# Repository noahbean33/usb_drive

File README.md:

# Smart USB Thumb Drive — 64 GB, 4-Layer PCB (KiCad)

A fully routed, manufacture-ready 64 GB USB thumb drive PCB designed from scratch in KiCad. This project demonstrates high-speed digital design, BGA escape routing, impedance-controlled differential pairs, and multi-layer power distribution — all within the physical constraints of a standard USB stick form factor.

## What This Project Is

This is a complete hardware design for a "smart" USB thumb drive built around:

- **RP2040** — Dual-core Arm Cortex-M0+ microcontroller (Raspberry Pi silicon)
- **MTFC64GAPALBH-IT** — 64 GB eMMC NAND flash in a 153-ball TFBGA package (0.5 mm pitch)
- **USB2244** — USB 2.0 to eMMC bridge controller
- **SY8253ADC** — Synchronous buck converter for regulated power
- **LM66100** — Dual ideal-diode OR-ing circuit for power path management
- **INA226** — High-side/low-side current and power monitor (I2C)
- **SSD1306** — 0.91" 128×32 OLED display for status readout
- **TMP119** — Digital temperature sensor
- **TVS diode arrays** — ESD protection on both USB ports

The drive is not just storage — the RP2040 provides programmable logic for monitoring power draw, temperature, and storage status via the OLED, making it a platform for embedded USB experimentation.

## How It Works

### Architecture

The schematic is split into hierarchical sheets for modularity:

| Sheet | Function |
|-------|----------|
| `oring_power` | Dual ideal-diode OR-ing (VBUS vs. external supply) |
| `buck_converter_power` | 3.3 V regulated rail from the OR'd input |
| `usb_bridge` | USB2244 bridge + ESD protection |
| `emmc_storage` | 64 GB eMMC with full 8-bit data bus |
| `rp2040` | MCU core, crystal, SWD, boot circuitry |
| `sensors` | INA226 current monitor + TMP119 temperature sensor |
| `gpio` | RP2040 breakout headers for development |

### PCB Stackup (4 layers)

| Layer | Purpose |
|-------|---------|
| F.Cu | Signal routing (USB diff pairs, eMMC data bus) |
| In1.Cu | Solid ground plane |
| In2.Cu | Power distribution plane |
| B.Cu | Signal routing (secondary) |

The dedicated ground and power planes provide low-impedance return paths and controlled impedance for high-speed signals.

## Key Design Decisions

### 1. BGA Escape Routing (Via-in-Pad)

The 153-ball eMMC package at 0.5 mm pitch cannot be escaped with surface traces alone. I used **via-in-pad** with 0.3 mm diameter / 0.15 mm drill vias placed directly on BGA pads, transitioning signals to inner layers. Custom DRC rules relax annular width minimums (0.075 mm) and clearances specifically within the BGA courtyard to allow this dense routing while maintaining DRC coverage everywhere else.

### 2. Impedance-Controlled USB 2.0 Differential Pairs

USB D+/D− pairs are routed as impedance-controlled differential pairs targeting 90 Ω differential impedance. Trace geometry was calculated using a stack-up impedance tool and verified against the fabricator's capabilities. Tight coupling is maintained throughout the route.

### 3. eMMC Data Bus Length Matching

The 8-bit parallel eMMC data bus is length-matched to ±3 mm (data lines) and ±5 mm (clock), meeting timing requirements for HS400-class operation. KiCad's tuning patterns (meander routing) are applied with 80% corner radius to minimize reflections.

### 4. Dual Ideal-Diode Power OR-ing

Rather than a simple regulator off VBUS, the power architecture uses two TI LM66100 ideal diodes in an OR-ing configuration. This allows the board to be powered from either USB port seamlessly, with near-zero reverse current and minimal voltage drop — critical for a bus-powered device with tight power budgets.

### 5. Custom DRC Rules

Instead of globally weakening design rules to accommodate BGA and fine-pitch ICs, I wrote **per-component DRC exceptions** in KiCad's custom rules language. Each rule is scoped by courtyard (`insideCourtyard`) so that strict defaults (0.1 mm clearance, standard annular widths) apply everywhere except where the design explicitly requires tighter geometry.

### 6. Teardrops and Reliability Features

Teardrops are enabled on all vias, PTH pads, and SMD pads to improve mechanical robustness and reduce stress risers during thermal cycling — important for a device that will be repeatedly plugged and unplugged.

## Repository Structure

```
├── Smart USB Drive - Course.kicad_pro    # KiCad project file
├── Smart USB Drive - Course.kicad_sch    # Top-level schematic
├── Smart USB Drive - Course.kicad_pcb    # PCB layout
├── Smart USB Drive - Course.kicad_dru    # Custom design rules
├── oring_power.kicad_sch                 # Power OR-ing sub-sheet
├── buck_converter_power.kicad_sch        # Buck converter sub-sheet
├── usb_bridge.kicad_sch                  # USB bridge sub-sheet
├── emmc_storage.kicad_sch                # eMMC storage sub-sheet
├── rp2040.kicad_sch                      # RP2040 MCU sub-sheet
├── sensors.kicad_sch                     # Sensors sub-sheet
├── gpio.kicad_sch                        # GPIO breakout sub-sheet
├── Gerbers-Smart_USB_v1.1/               # Production-ready Gerber files
├── Datasheets/                           # Component datasheets
└── Library/                              # Custom symbols, footprints, 3D models
```

## Tools Used

- **KiCad 8** — Schematic capture, PCB layout, DRC, and Gerber generation
- **NextPCB HQDFM** — Design-for-manufacturing verification and impedance stack-up calculation

## Skills Demonstrated

- Multi-layer PCB design with impedance control
- BGA fanout and via-in-pad escape routing
- High-speed differential pair routing (USB 2.0)
- Parallel bus length matching with meander tuning
- Hierarchical schematic design for complex systems
- Power architecture design (ideal-diode OR-ing, buck regulation)
- Custom DRC rule authoring in KiCad
- Full manufacturing output generation (Gerbers, BOM, pick-and-place)

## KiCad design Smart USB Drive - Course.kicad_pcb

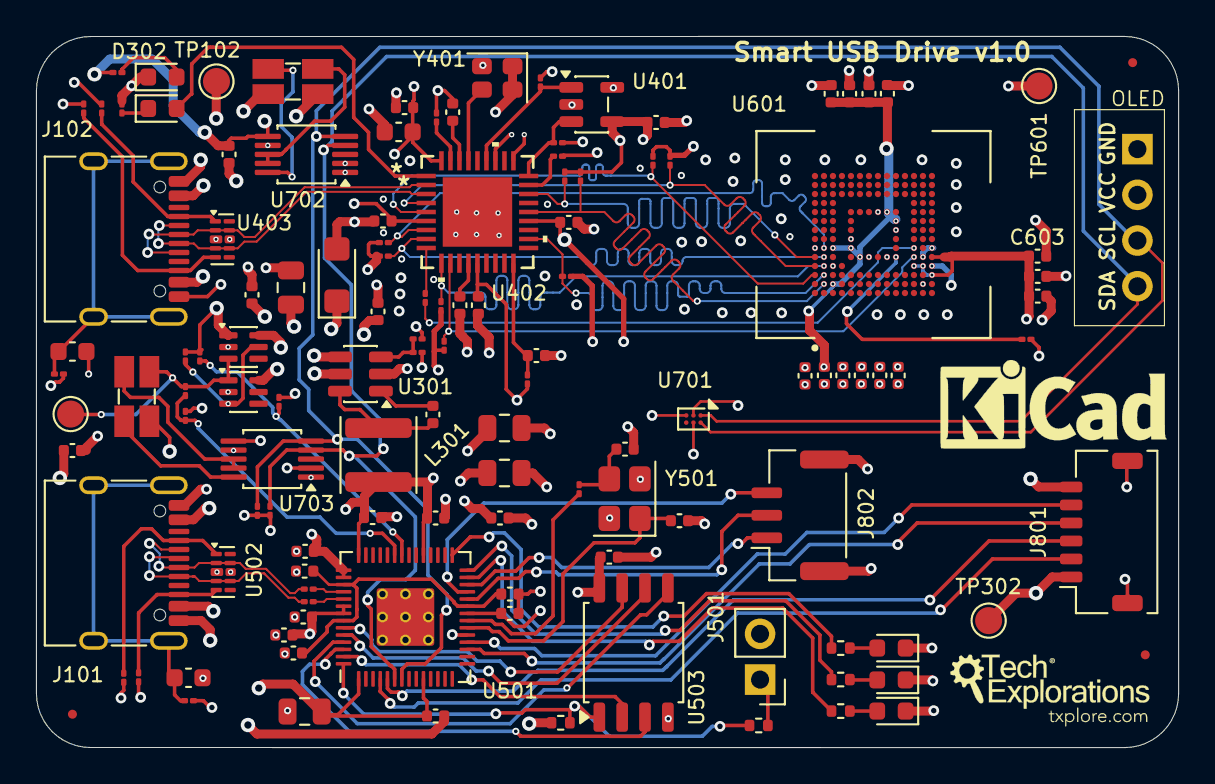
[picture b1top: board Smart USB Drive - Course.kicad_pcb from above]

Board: 4 copper layers, 63.5 x 39.5 mm, 122 parts (0 on the bottom side), 77 nets.

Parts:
C101, C102: 2.2n 100V; C_0603_1608Metric
C201, C303, C403, C404, C602, C612: 1u 10V; C_0402_1005Metric
C301, C402, C405, C406, C407, C408, C601, C608, C609, C610, C611: 0.1u 10V; C_0402_1005Metric
C302, C304, C305: 22u 10V; C_0805_2012Metric
C401: 100n 10V; C_0402_1005Metric
C409: 4.7u 10V; C_0603_1608Metric
C501, C502: 15p 10V; C_0402_1005Metric
C503, C504, C506, C508, C509, C510, C511, C512, C513, C515: 1n / 10V; C_0402_1005Metric
C505, C507: 1u /10V; C_0402_1005Metric
C514: 10u/10V; C_0805_2012Metric
C603, C604, C605, C606, C607, C613: 2.2u 10V; C_0402_1005Metric
C701, C702: 1u/10V; C_0402_1005Metric
D301: SMF5V0A; D_SMF
D302: LED RED; LED_0603_1608Metric
D401, D801, D802, D803: LED; LED_0603_1608Metric
DS701: OLED_SSD1306_0p91_128x32_I2C; SSD1306-0.91-OLED-4pin-128x32
J101, J102: USB_C_Receptacle_USB2.0_16P; USB_C_Receptacle_XKB_U262-16XN-4BVC11
J501: Conn_01x02; PinHeader_1x02_P2.54mm_Vertical
J801: Conn_01x06; JST_SHL_SM06B-SHLS-TF_1x06-1MP_P1.00mm_Horizontal
J802: Conn_01x03; JST_GH_SM03B-GHS-TB_1x03-1MP_P1.25mm_Horizontal
L301: 2.2uH/4,3A; L_Sunlord_SWPA4020S
R101, R102: 1M/1%; R_01005_0402Metric
R103, R104, R105, R106: 5.5K /1%; R_01005_0402Metric
R107, R108: 2m/1%; R_Shunt_Ohmite_LVK12
R201, R203, R205, R301: 100K/1%; R_01005_0402Metric
R202, R204: 150K/1%; R_01005_0402Metric
R302: 22.1K/1%; R_01005_0402Metric
R303, R503: 1K/1%; R_01005_0402Metric
R401, R402, R404, R609, R612: 10K/1%; R_01005_0402Metric
R403: 12K /1%; R_01005_0402Metric
R405: 330/1%; R_01005_0402Metric
R406: 10K /1%; R_01005_0402Metric
R501, R502: 27.4/1%; R_01005_0402Metric
R504, R801, R802, R803: 1k; R_0402_1005Metric
R505: DNF; R_0402_1005Metric
R506, R507: 4.7K/1%; R_01005_0402Metric
R601, R602, R603, R604, R605, R606, R607, R608: 47K/1%; R_01005_0402Metric
R610: 22/1%; R_01005_0402Metric
TP101, TP102, TP302, TP601: TestPoint; TestPoint_Pad_D1.5mm
U201, U202: LM66100DCK; SOT-363_SC-70-6
U301: SY8253ADC; TSOT-23-6
U401: AT24CS04-STUM; SOT-23-5
U402: USB2244-AEZG-06; QFN36_6X6MC_MCH
U403, U502: D3V3XA4B10LP; Diodes_UDFN-10_1x2.5mm_P0.5mm
U501: RP2040; RP2040-QFN-56
U503: W25Q128JVS; SOIC-8_5.3x5.3mm_P1.27mm
U601: MTFC64GAPALBH-IT; BGA153N50P14X14_1300X1150X110N
U701: TMP119AIYBGR; Texas_DSBGA-6_0.95x1.488mm_Layout2x3_P0.4mm
U702, U703: INA226; TSSOP-10_3x3mm_P0.5mm
Y401: SG-210STF; Oscillator_SMD_SeikoEpson_SG210-4Pin_2.5x2.0mm
Y501: Crystal_GND24; Crystal_SMD_3225-4Pin_3.2x2.5mm

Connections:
+1V1: C503.1, C504.1, C505.1, U501.23 (DVDD), U501.45 (VREG_VOUT), U501.50 (DVDD)
/ORING_POWER/NOTIFY_3V3_CON1: R201.2, R202.1, U501.36 (GPIO24)
/ORING_POWER/NOTIFY_3V3_CON2: R203.2, R204.1, U501.37 (GPIO25)
/ORING_POWER/ORING_5V: C201.1, C301.1, C302.1, D301.1 (A1), U201.6 (VOUT), U202.6 (VOUT), U301.4 (EN), U301.5 (VIN)
/RP2040/GPIO14: J801.4, U501.17 (GPIO14)
/RP2040/GPIO15: J801.5, U501.18 (GPIO15)
/RP2040/I2C0_SCL: DS701.3 (SCL), R507.1, U501.7 (GPIO5), U701.A2 (SCL), U702.5 (SCL), U703.5 (SCL)
/RP2040/I2C0_SDA: DS701.4 (SDA), R506.1, U501.6 (GPIO4), U701.A1 (SDA), U702.4 (SDA), U703.4 (SDA)
/RP2040/I2C_SCL: J801.3, U501.5 (GPIO3)
/RP2040/I2C_SDA: J801.2, U501.4 (GPIO2)
/RP2040/LED_A: R801.2, U501.27 (GPIO16)
/RP2040/LED_B: R802.2, U501.28 (GPIO17)
/RP2040/LED_C: R803.2, U501.29 (GPIO18)
/RP2040/QSPI_SCLK: U501.52 (QSPI_SCLK), U503.6 (CLK)
/RP2040/QSPI_SD0: U501.53 (QSPI_SD0), U503.5 (DI/IO_{0})
/RP2040/QSPI_SD1: U501.55 (QSPI_SD1), U503.2 (DO/IO_{1})
/RP2040/QSPI_SD2: U501.54 (QSPI_SD2), U503.3 (~WP/IO_{2})
/RP2040/QSPI_SD3: U501.51 (QSPI_SD3), U503.7 (~HOLD/~RESET/IO_{3})
/RP2040/QSPI_SS: R504.1, R505.2, U501.56 (QSPI_SS), U503.1 (~CS)
/RP2040/RP_USB_D+: J101.A6 (D+), J101.B6 (D+), R501.2, U502.4, U502.7 (NC)
/RP2040/RP_USB_D-: J101.A7 (D-), J101.B7 (D-), R502.2, U502.2
/RP2040/RP_XIN: C501.1, U501.20 (XIN), Y501.1
/RP2040/RP_XOUT: R503.2, U501.21 (XOUT)
/RP2040/RUN: J802.1, U501.26 (RUN)
/RP2040/SWCLK: J802.2, U501.24 (SWCLK)
/RP2040/SWD: J802.3, U501.25 (SWD)
/RP2040/~USB_BOOT: J501.1, R504.2
/USB_BRIDGE/MMCD0: R601.2, U402.5 (SD_D0), U601.A3 (DAT0)
/USB_BRIDGE/MMCD1: R602.2, U402.4 (SD_D1), U601.A4 (DAT1)
/USB_BRIDGE/MMCD2: R603.2, U402.25 (SD_D2), U601.A5 (DAT2)
/USB_BRIDGE/MMCD3: R604.2, U402.23 (SD_D3), U601.B2 (DAT3)
/USB_BRIDGE/MMCD4: R605.2, U402.20 (SD_D4), U601.B3 (DAT4)
/USB_BRIDGE/MMCD5: R606.2, U402.10 (SD_D5), U601.B4 (DAT5)
/USB_BRIDGE/MMCD6: R607.2, U402.8 (SD_D6), U601.B5 (DAT6)
/USB_BRIDGE/MMCD7: R608.2, U402.7 (SD_D7), U601.B6 (DAT7)
/USB_BRIDGE/MMC_CLK: R610.2, U402.9 (SD_CLK)
/USB_BRIDGE/SCL_USB2244: R404.2, U401.1 (SCL), U402.31 (TXD/SCK)
/USB_BRIDGE/SDA_USB2244: R402.2, U401.3 (SDA), U402.27 (RXD/SDA)
/USB_BRIDGE/STORAGE_USB+: J102.A6 (D+), J102.B6 (D+), U402.2 (USB+), U403.2, U403.9 (NC)
/USB_BRIDGE/STORAGE_USB-: J102.A7 (D-), J102.B7 (D-), U402.3 (USB-), U403.4, U403.7 (NC)
/USB_CC1_CON1: J102.A5 (CC1), R105.2, U403.1
/USB_CC1_CON2: J101.A5 (CC1), R103.2, U502.1
/USB_CC2_CON1: J102.B5 (CC2), R106.1, U403.5
/USB_CC2_CON2: J101.B5 (CC2), R104.1, U502.5
/VBUS_MCU: R107.4, R203.1, TP101.1 (1_1), U201.3 (~CE), U202.1 (VIN)
/VBUS_MCU_IN+: R107.2, U703.10 (Vin+)
/VBUS_MCU_IN-: R107.3, U703.8 (Vbus), U703.9 (Vin-)
/VBUS_STORAGE: R108.4, R201.1, R205.1, TP102.1 (1_1), U201.1 (VIN)
/VBUS_STORAGE_IN+: R108.2, U702.10 (Vin+)
/VBUS_STORAGE_IN-: R108.3, U702.8 (Vbus), U702.9 (Vin-)
/eMMC_STORAGE/MMC_CLK_L: R610.1, U601.M6 (CLK)
/eMMC_STORAGE/MMC_CMD_L: R612.2, U402.11 (SD_CMD), U601.M5 (CMD)
GND: C101.2, C102.2, C201.2, C301.2, C302.2, C304.1, C304.2, C305.1, C305.2, C401.1, C401.2, C402.2, C403.1, C404.1, C405.1, C405.2, C406.1, C406.2, C407.1, C407.2, C408.1, C408.2, C409.1, C409.2, C501.2, C502.2, C503.2, C504.2, C505.2, C506.1, C506.2, C507.1, C507.2, C508.1, C508.2, C509.1, C509.2, C510.1, C510.2, C511.1, C511.2, C512.1, C512.2, C513.1, C513.2, C514.1, C514.2, C515.1, C515.2, C601.1, C601.2, C602.1, C602.2, C603.1, C603.2, C604.1, C604.2, C605.1, C605.2, C606.1, C606.2, C607.1, C607.2, C608.1, C608.2, C609.1, C609.2, C610.1, C610.2, C611.1, C611.2, C612.1, C612.2, C613.1, C613.2, C701.1, C701.2, C702.1, C702.2, D301.2 (A2), D302.1 (K), D801.1 (K), D802.1 (K), D803.1 (K), DS701.1 (GND), J101.A1 (GND), J101.A12 (GND), J101.B1 (GND), J101.B12 (GND), J102.A1 (GND), J102.A12 (GND), J102.B1 (GND), J102.B12 (GND), J501.2, J801.1, J801.6, J801.7 (MP1), J801.8 (MP2), J802.MP, L301.2, R101.2, R102.2, R103.1, R104.2, R105.1, R106.2, R202.2, R204.2, R301.1, R302.2, R303.1, R401.1, R402.1, R403.2, R404.1, R405.1, R406.1, R505.1, R506.2, R507.2, R601.1, R602.1, R603.1, R604.1, R605.1, R606.1, R607.1, R608.1, R609.2, R612.1, TP302.1 (1_1), TP601.1 (1_1), U201.2 (GND), U202.2 (GND), U301.2 (GND), U401.2 (GND), U401.4 (VCC), U401.5 (WP), U402.6 (VDD33), U402.14 (VDD33), U402.22 (VDD33), U402.28 (TEST), U402.30 (SD_WP), U402.36 (VDDA33), U402.37 (EPAD), U403.3 (VSS), U403.8 (VSS), U501.1 (IOVDD), U501.10 (IOVDD), U501.19 (TESTEN), U501.22 (IOVDD), U501.33 (IOVDD), U501.42 (IOVDD), U501.43 (ADC_AVDD), U501.44 (VREG_IN), U501.48 (USB_VDD), U501.49 (IOVDD), U501.57 (GND), U502.3 (VSS), U502.8 (VSS), U503.4 (GND), U503.8 (VCC), U601.A6 (VSS), U601.C2 (VDDIM), U601.C4 (VSSQ), U601.C6 (VCCQ), U601.E6 (VCC), U601.E7 (VSS__1), U601.F5 (VCC__1), U601.G5 (VSS__2), U601.H10 (VSS__3), U601.J5 (VSS__4), U601.J10 (VCC__2), U601.K8 (VSS__5), U601.K9 (VCC__3), U601.M4 (VCCQ__1), U601.N2 (VSSQ__1), U601.N4 (VCCQ__2), U601.N5 (VSSQ__2), U601.P3 (VCCQ__3), U601.P4 (VSSQ__3), U601.P5 (VCCQ__4), U601.P6 (VSSQ__4), U701.B1 (V+), U701.B2 (GND), U701.C1 (ADD0), U702.1 (A1), U702.2 (A0), U702.6 (VS), U702.7 (GND), U703.1 (A1), U703.2 (A0), U703.6 (VS), U703.7 (GND), Y401.1 (~ST), Y401.2 (GND), Y401.4 (Vcc), Y501.2 (G), Y501.4 (G)
unnamed: C502.1, R503.1, Y501.3
unnamed: D302.2 (A), R303.2
unnamed: D401.2 (A), U402.1 (LED)
unnamed: D401.1 (K), R405.2
unnamed: D801.2 (A), R801.1
unnamed: D802.2 (A), R802.1
unnamed: D803.2 (A), R803.1
unnamed: C101.1, J101.SH (SHIELD), R101.1
unnamed: J101.A4 (VBUS), J101.A9 (VBUS), J101.B4 (VBUS), J101.B9 (VBUS), R107.1
unnamed: C102.1, J102.SH (SHIELD), R102.1
unnamed: J102.A4 (VBUS), J102.A9 (VBUS), J102.B4 (VBUS), J102.B9 (VBUS), R108.1
unnamed: R205.2, U201.5 (ST), U202.3 (~CE)
unnamed: C303.1, U301.1 (BOOST)
unnamed: R301.2, R302.1, U301.3 (FB)
unnamed: C303.2, L301.1, U301.6 (SW)
unnamed: R403.1, U402.35 (RBIAS)
unnamed: C402.1, R401.2, U402.18 (RESET_N)
unnamed: R406.2, U402.26 (SD_NCD)
unnamed: U402.33 (XTAL1(CLKIN)), Y401.3 (OUT)
unnamed: C403.2, U402.13 (VDD18)
unnamed: C404.2, U402.34 (VDD18PLL)
unnamed: R502.1, U501.46 (USB_DM)
unnamed: R501.1, U501.47 (USB_DP)
unnamed: R609.1, U601.K5 (RST_N)

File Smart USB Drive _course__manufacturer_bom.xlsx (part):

Reference | Quantity | Value | Footprint | MPN | Manufacturer | Description | Distributor | Unit Price | Currency | Stock | Notes
U301 | 1 | SY8253ADC | Package_TO_SOT_SMD:TSOT-23-6 | SY8253ADC | Silergy |  | Karl Kruse GmbH | 0 | USD | 10000
R501,R502 | 2 | 27.4/1% | Resistor_SMD:R_01005_0402Metric | RC0402FR-0727R4L | YAGEO | RES 27.4 OHM 1% 1/16W 0402 | digikey |  | USD | 762370
U403,U502 | 2 | D3V3XA4B10LP | Package_DFN_QFN:Diodes_UDFN-10_1x2.5mm_P0.5mm | D3V3XA4B10LP7 | Diodes Incorporated | Dataline Protection PP U-DFN2510-10 T&R | RS UK | 0.0675 | USD | 2825
U702,U703 | 2 | INA226 | Package_SO:TSSOP-10_3x3mm_P0.5mm | INA226AIDGST | Texas Instruments |  | Ozdisan | 2.5958 | USD | 0
U402 | 1 | USB2244-AEZG-06 | footprints:QFN36_6X6MC_MCH | USB2244AEZG06TR | Microchip Technology | Ultra Fast USB 2.0 SD/MMC Flash Media Controller | Microchip Technology Inc | 2.51 | USD | 3000
J802 | 1 | Conn_01x03 | Connector_JST:JST_GH_SM03B-GHS-TB_1x03-1MP_P1.25mm_Horizontal | SM03BGHSTBLFSN | JST |  | Heilind Americas | 0.1721 | USD | 0
U501 | 1 | RP2040 | RP2040_minimal_r2:RP2040-QFN-56 | SC0914(13) | Raspberry Pi | IC MCU 32BIT EXT MEM 56QFN | digikey |  | USD | 114012
R405 | 1 | 330/1% | Resistor_SMD:R_01005_0402Metric | CRCW04023K30FKTD | Vishay Intertechnology | Thick Film Resistors - SMD 3.3k ohm 1% | TTI Americas | 0.0168 | USD | 10000
R506,R507 | 2 | 4.7K/1% | Resistor_SMD:R_01005_0402Metric | RC0402FR-074K7L | YAGEO | RES 4.7K OHM 1% 1/16W 0402 | digikey |  | USD | 2530392
R406 | 1 | 10K /1% | Resistor_SMD:R_01005_0402Metric | CRCW040210K0FKED | Vishay Intertechnology | Thick Film Resistors - SMD 10k ohm 1% | TTI Americas | 0.0013 | USD | 9120000
R504,R801,R802,R803 | 4 | 1k | Resistor_SMD:R_0402_1005Metric | 1K0402 | Not Specified |  | Cyclops Electronics | 0 | USD | 940
R403 | 1 | 12K /1% | Resistor_SMD:R_01005_0402Metric | CRCW040212K0FKED | Vishay Intertechnology | Thick Film Resistors - SMD 12k ohm 1% | TTI Americas |  | USD | 230000
C514 | 1 | 10u/10V | Capacitor_SMD:C_0805_2012Metric | CL21A106KPFNNNE | Samsung Electro-Mechanics | CAP CER 10UF 10V X5R 0805 | digikey |  | USD | 93830
R303,R503 | 2 | 1K/1% | Resistor_SMD:R_01005_0402Metric | CRCW040251K1FKED | Vishay Intertechnology | Thick Film Resistors - SMD 51.1k ohm 1% | TTI Americas | 0.0018 | USD | 530000
U401 | 1 | AT24CS04-STUM | Package_TO_SOT_SMD:SOT-23-5 | AT24CS04STUMT | Microchip Technology | EEPROM - Serial-I²C - 4Kbit (512 x 8) - 1.8V/2.5V/3.3V/5V - 5-Pin SOT-23 - Tape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 | Master Electronics | 0.2921 | USD | 20000
U201,U202 | 2 | LM66100DCK | Package_TO_SOT_SMD:SOT-363_SC-70-6 | LM66100DCKR | Texas Instruments | IC OR CTRLR IDEAL DIODE SC70-6 | digikey |  | USD | 13643
R610 | 1 | 22/1% | Resistor_SMD:R_01005_0402Metric | 22104028 | Molex | KK 100 HDR FLAT VERT 30 AU 2CKT | RS Americas | 0.477 | USD | 0
R401,R402,R404,R609,R612 | 5 | 10K/1% | Resistor_SMD:R_01005_0402Metric | TNPW040210K1BEED | Vishay Intertechnology | Thin Film Resistors - SMD 10.1k ohm .1% 25ppm 1/10w | TTI Americas |  | USD | 0
R302 | 1 | 22.1K/1% | Resistor_SMD:R_01005_0402Metric | RC0402FR-0722K1L | YAGEO | RES 22.1K OHM 1% 1/16W 0402 | digikey |  | USD | 407819
R202,R204 | 2 | 150K/1% | Resistor_SMD:R_01005_0402Metric | CRG0402J150K10 | TE Connectivity | Thick Film Resistors - SMD crg0402 5% 150k | TTI Americas |  | USD | 0
Y401 | 1 | SG-210STF | Oscillator:Oscillator_SMD_SeikoEpson_SG210-4Pin_2.5x2.0mm | SG210SCB16000000MHzBQ33210B70000412 | Seiko Coporation |  | CoreStaff | 0.953 | USD | 2
R201,R203,R205,R301 | 4 | 100K/1% | Resistor_SMD:R_01005_0402Metric | M3253502E1B100KZMB | KEMET |  | TTI Americas |  | USD | 0
R107,R108 | 2 | 2m/1% | Resistor_SMD:R_Shunt_Ohmite_LVK12 | LVK12R010DER | Ohmite | Rohs Res., 0.01 Ohm, 1/2W, 0.5%, 1206 | Sensible Micro | 0 | USD | 466
R601,R602,R603,R604,R605,R606,R607,R608 | 8 | 47K/1% | Resistor_SMD:R_01005_0402Metric | RC0402FR-0747KL | YAGEO | RES 47K OHM 1% 1/16W 0402 | digikey |  | USD | 1409431
J801 | 1 | Conn_01x06 | Connector_JST:JST_SHL_SM06B-SHLS-TF_1x06-1MP_P1.00mm_Horizontal | SM06BSHLSTFLFSN | JST | CUT TAPE - 6-POS SHL CONN 1.0MM PITCH WtoB CRIMP ST | Interstate Connecting Components | 0.6487000000000001 | USD | 1194
L301 | 1 | 2.2uH/4,3A | Inductor_SMD:L_Sunlord_SWPA4020S | SWPA4020S4R7MT | sunlord |  | Kepictronics | 0 | USD | 2740
R103,R104,R105,R106 | 4 | 5.5K /1% | Resistor_SMD:R_01005_0402Metric | CRCW040225K5FKED | Vishay Intertechnology | Thick Film Resistors - SMD 25.5k ohm 1% | TTI Americas | 0.002 | USD | 0
C503,C504,C506,C508,C509,C510,C511,C512,C513,C515 | 10 | 1n / 10V | Capacitor_SMD:C_0402_1005Metric | C0402C102K8RACTU | KEMET | Multilayer Ceramic Capacitors MLCC - SMD/SMT 1000pf 10v 10% 0402 | TTI Americas | 0.0035 | USD | 300000
R101,R102 | 2 | 1M/1% | Resistor_SMD:R_01005_0402Metric | CRCW04021M10FKED | Vishay Intertechnology | Thick Film Resistors - SMD 1.1m ohm 1% | TTI Americas | 0.0018 | USD | 720000
C409 | 1 | 4.7u 10V | Capacitor_SMD:C_0603_1608Metric | C0603C475K8PAC7867 | KEMET | Multilayer Ceramic Capacitors MLCC - SMD/SMT 4.7uf 10v 10% 0603 | TTI Americas | 0.04 | USD | 244000
U601 | 1 | MTFC64GAPALBH-IT | footprints:BGA153N50P14X14_1300X1150X110N | MTFC64GAPALBHIT | Micron Technology | Emmc512G, Tray Rohs Compliant: Yes |Micron Technology MTFC64GAPALBH-IT | Newark | 0 | USD | 0
C603,C604,C605,C606,C607,C613 | 6 | 2.2u 10V | Capacitor_SMD:C_0402_1005Metric | C0402C225M8PACTU | KEMET | Multilayer Ceramic Capacitors MLCC - SMD/SMT 2.2uf 10v 20% 0402 | TTI Americas | 0.047 | USD | 950000
D302 | 1 | LED RED | LED_SMD:LED_0603_1608Metric | Q62702P5187 | ams OSRAM | Single Color LEDs s red smd led chip led 0603 | TTI Americas | 0.0223 | USD | 4000
C501,C502 | 2 | 15p 10V | Capacitor_SMD:C_0402_1005Metric | C0402C150J8GACTU | KEMET | Multilayer Ceramic Capacitors MLCC - SMD/SMT 15pf 10v 5% 0402 | TTI Americas |  | USD | 0
C401 | 1 | 100n 10V | Capacitor_SMD:C_0402_1005Metric | C0402C104K8RAC7867 | KEMET | Multilayer Ceramic Capacitors MLCC - SMD/SMT .1uf 10v 10% 0402 | TTI Americas | 0.0055 | USD | 5290000
C505,C507 | 2 | 1u /10V | Capacitor_SMD:C_0402_1005Metric | C0402C105K8PACTU | KEMET | Multilayer Ceramic Capacitors MLCC - SMD/SMT 1.0uf 10v 10% 0402 | TTI Americas | 0.0161 | USD | 510000
C302,C304,C305 | 3 | 22u 10V | Capacitor_SMD:C_0805_2012Metric | C0805C226M8PACTU | KEMET | Multilayer Ceramic Capacitors MLCC - SMD/SMT 22uf 10v 20% 0805 | TTI Americas | 0.1 | USD | 75000
C101,C102 | 2 | 2.2n 100V | Capacitor_SMD:C_0603_1608Metric | C0603C222K1RACTU | KEMET | Multilayer Ceramic Capacitors MLCC - SMD/SMT 2200pf 100v 10% 0603 | TTI Americas |  | USD | 96000
C201,C303,C403,C404,C602,C612 | 6 | 1u 10V | Capacitor_SMD:C_0402_1005Metric | C0402C105K8PACTU | KEMET | Multilayer Ceramic Capacitors MLCC - SMD/SMT 1.0uf 10v 10% 0402 | TTI Americas | 0.0161 | USD | 510000
C301,C402,C405,C406,C407,C408,C601,C608,C609,C610,C611 | 11 | 0.1u 10V | Capacitor_SMD:C_0402_1005Metric | C0402C104K8RAC7867 | KEMET | Multilayer Ceramic Capacitors MLCC - SMD/SMT .1uf 10v 10% 0402 | TTI Americas | 0.0055 | USD | 5290000
U503 | 1 | W25Q128JVS | Package_SO:SOIC-8_5.3x5.3mm_P1.27mm | W25Q128JVSIMTR | Winbond Electronics Corporation |  | EPI Tech | 4.375 | USD | 3505
U701 | 1 | TMP119AIYBGR | Package_BGA:Texas_DSBGA-6_0.95x1.488mm_Layout2x3_P0.4mm | TMP119AIYBGR | Texas Instruments |  | AERI | 4.055 | USD | 8308
J101,J102 | 2 | USB_C_Receptacle_USB2.0_16P | Connector_USB:USB_C_Receptacle_XKB_U262-16XN-4BVC11 | 2171790003 | Molex | USB CONN, R/A, TYPE C 2.0, RCPT, 16P; | element14 Singapore | 0.8016 | USD | 624
D401,D801,D802,D803 | 4 | LED | LED_SMD:LED_0603_1608Metric | APTD1608LSURCK | Kingbright |  | AERI | 0.08599999999999999 | USD | 27003
D301 | 1 | SMF5V0A | Diode_SMD:D_SMF | SMF5V0AHE3A08 | Vishay Intertechnology |  | EBV Elektronik | 0 | USD | 0
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
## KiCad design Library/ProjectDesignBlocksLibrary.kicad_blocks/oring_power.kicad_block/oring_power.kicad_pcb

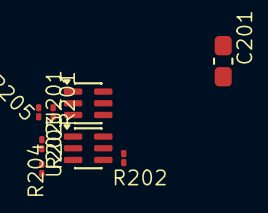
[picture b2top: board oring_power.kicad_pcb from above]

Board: 4 copper layers, 8 parts (0 on the bottom side), 7 nets, no tracks yet.

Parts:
C201: 1u 10V; C_0603_1608Metric_Pad1.08x0.95mm_HandSolder
R201, R203, R205: 100K/1%; R_01005_0402Metric
R202, R204: 150K/1%; R_01005_0402Metric
U201, U202: LM66100DCK; SOT-363_SC-70-6

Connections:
/ORING_POWER/NOTIFY_3V3_CON1: R201.2, R202.1
/ORING_POWER/NOTIFY_3V3_CON2: R203.2, R204.1
/ORING_POWER/ORING_5V: C201.1, U201.6 (VOUT), U202.6 (VOUT)
/VBUS_MCU: R203.1, U201.3 (~CE), U202.1 (VIN)
/VBUS_STORAGE: R201.1, R205.1, U201.1 (VIN)
GND: C201.2, R202.2, R204.2, U201.2 (GND), U202.2 (GND)
unnamed: R205.2, U201.5 (ST), U202.3 (~CE)

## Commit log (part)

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2026-05-28 initialized schematic
2026-06-23 implemented project
